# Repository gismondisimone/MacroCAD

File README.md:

# MacroCAD - More Numbers Is ALWAYS Better

### A Tiny, Industrial Look, Feature-Packed Macropad for Maximum Efficiency

*(or just a cool number-pad).*

---

## Renders

---
## BOM
All the bits and pieces needed can be found **[here](/BOM.md)**.

---

## What is This?
It's a **custom macropad** built with the **Seeed Studio XIAO RP2040**, **QMK firmware**. It's designed by a CAD user for CAD users. The design is as cool as fragile.

### Features:
- **3x4 Matrix** - Just numbers and a dot key and enter key.
- **OLED Display** - It's a cool add-on though I will update its functions in the future.
- **QMK Firmware** - Open-source, because we like freedom.

---

## How It Works:
This macropad runs **QMK**, which means you get:
- **Custom Keymaps** - Map macros, media keys, or even full-blown scripts.
- **Dynamic Layers** - More functions per button? Yes, please.
- **Display Support** - A cat that reminds you to work on your project? An integration with Hackatime that shows up your hours spent on designing.

---

## Default Keymap:
*(Change it if you want, you could delete the enter key and put a shortcut for your CAD software).*

### **3x4 Button Layout:**
|Row  | Key 1 | key 2 | Key 3 |
|-----|-------|-------|-------|
|**1**|   7   |   8   |   9   |
|**2**|   4   |   5   |   6   |
|**3**|   1   |   2   |   3   |
|**4**|   0   |   .   |  ent  |

---

## How to Build It:

**Step 1** - Put the inserts in the holes on the bottom part.

**Step 2** - Align holes on the PCB to the holes on the bottom part.

**Step 3** - Align holes on the top part to the holes on the PCB.

**Step 4** - Put two M4x25 screws in the holes.

---

## Why?
I built this macropad for [Hackpad](https://hackpad.hackclub.com/)-an awesome Hack Club YSWS project. With the (hopeful) funding provided by the project, I wanted to create something that's as practical as it is professional. Whether you're designing your favorite projects, this macropad is my way of saying:

#### why settle for ordinary when you can hack something extraordinary?

## The Biggest Challenge:
It's my second time designing a PCB, I'm slowly improving.

---

## Future Plans (Maybe):
- Encoder?
- Bluetooth support? (Would need a battery)
- Improving the design with aluminum frame, LEDS?

---

## Contribute  
Want to make it better? Open a PR, suggest a feature, or just yell at me on GitHub.

---

## Disclaimer  
This project is 100% free, open-source, and powered by **vibes**. If it breaks, explodes, or opens a black hole, **that's on you.**

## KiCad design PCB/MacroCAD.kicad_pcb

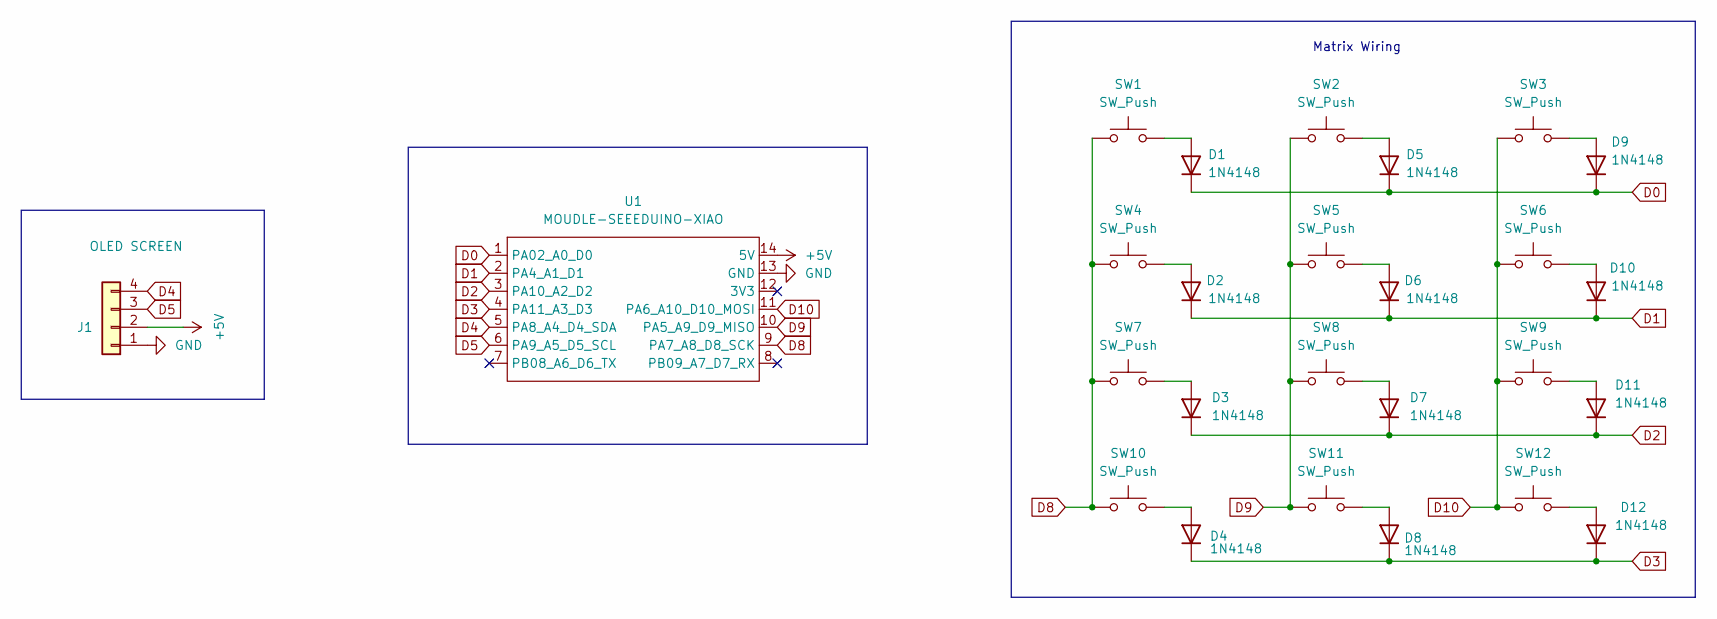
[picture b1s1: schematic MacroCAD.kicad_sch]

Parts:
D1, D2, D3, D4, D5, D6, D7, D8, D9, D10, D11, D12: 1N4148; D_DO-35_SOD27_P7.62mm_Horizontal
J1: OLED SCREEN; PinSocket_1x04_P2.54mm_Vertical
SW1, SW2, SW3, SW4, SW5, SW6, SW7, SW8, SW9, SW10, SW11, SW12: SW_Push; MX-Solderable-1.25U
U1: MOUDLE-SEEEDUINO-XIAO; XIAO-Generic-Hybrid-14P-2.54-21X17.8MM

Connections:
+5V: J1.2, U1.14 (5V)
D0: D1.1 (K), D5.1 (K), D9.1 (K), U1.1 (PA02_A0_D0)
D1: D2.1 (K), D6.1 (K), D10.1 (K), U1.2 (PA4_A1_D1)
D2: D3.1 (K), D7.1 (K), D11.1 (K), U1.3 (PA10_A2_D2)
D3: D4.1 (K), D8.1 (K), D12.1 (K), U1.4 (PA11_A3_D3)
D4: J1.4, U1.5 (PA8_A4_D4_SDA)
D5: J1.3, U1.6 (PA9_A5_D5_SCL)
D8: SW1.1, SW4.1, SW7.1, SW10.1, U1.9 (PA7_A8_D8_SCK)
D9: SW2.1, SW5.1, SW8.1, SW11.1, U1.10 (PA5_A9_D9_MISO)
D10: SW3.1, SW6.1, SW9.1, SW12.1, U1.11 (PA6_A10_D10_MOSI)
GND: J1.1, U1.13 (GND)
unnamed: D1.2 (A), SW1.2
unnamed: D2.2 (A), SW4.2
unnamed: D3.2 (A), SW7.2
unnamed: D4.2 (A), SW10.2
unnamed: D5.2 (A), SW2.2
unnamed: D6.2 (A), SW5.2
unnamed: D7.2 (A), SW8.2
unnamed: D8.2 (A), SW11.2
unnamed: D9.2 (A), SW3.2
unnamed: D10.2 (A), SW6.2
unnamed: D11.2 (A), SW9.2
unnamed: D12.2 (A), SW12.2

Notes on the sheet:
Matrix Wiring

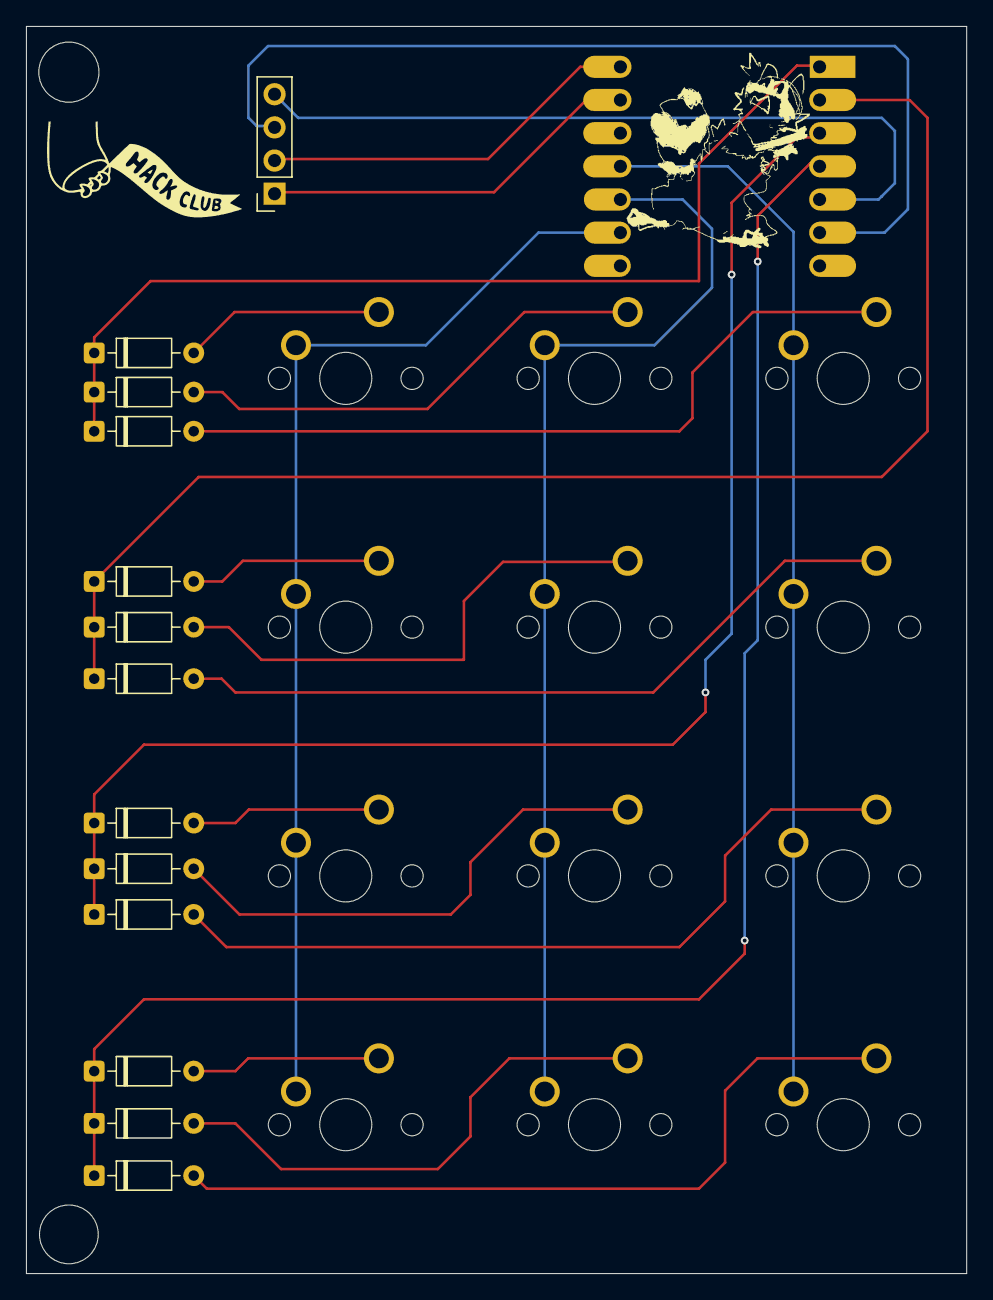
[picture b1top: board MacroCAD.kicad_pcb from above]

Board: 2 copper layers, 72.0 x 95.5 mm, 27 parts (1 on the bottom side), 23 nets.

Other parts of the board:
G: LOGO
